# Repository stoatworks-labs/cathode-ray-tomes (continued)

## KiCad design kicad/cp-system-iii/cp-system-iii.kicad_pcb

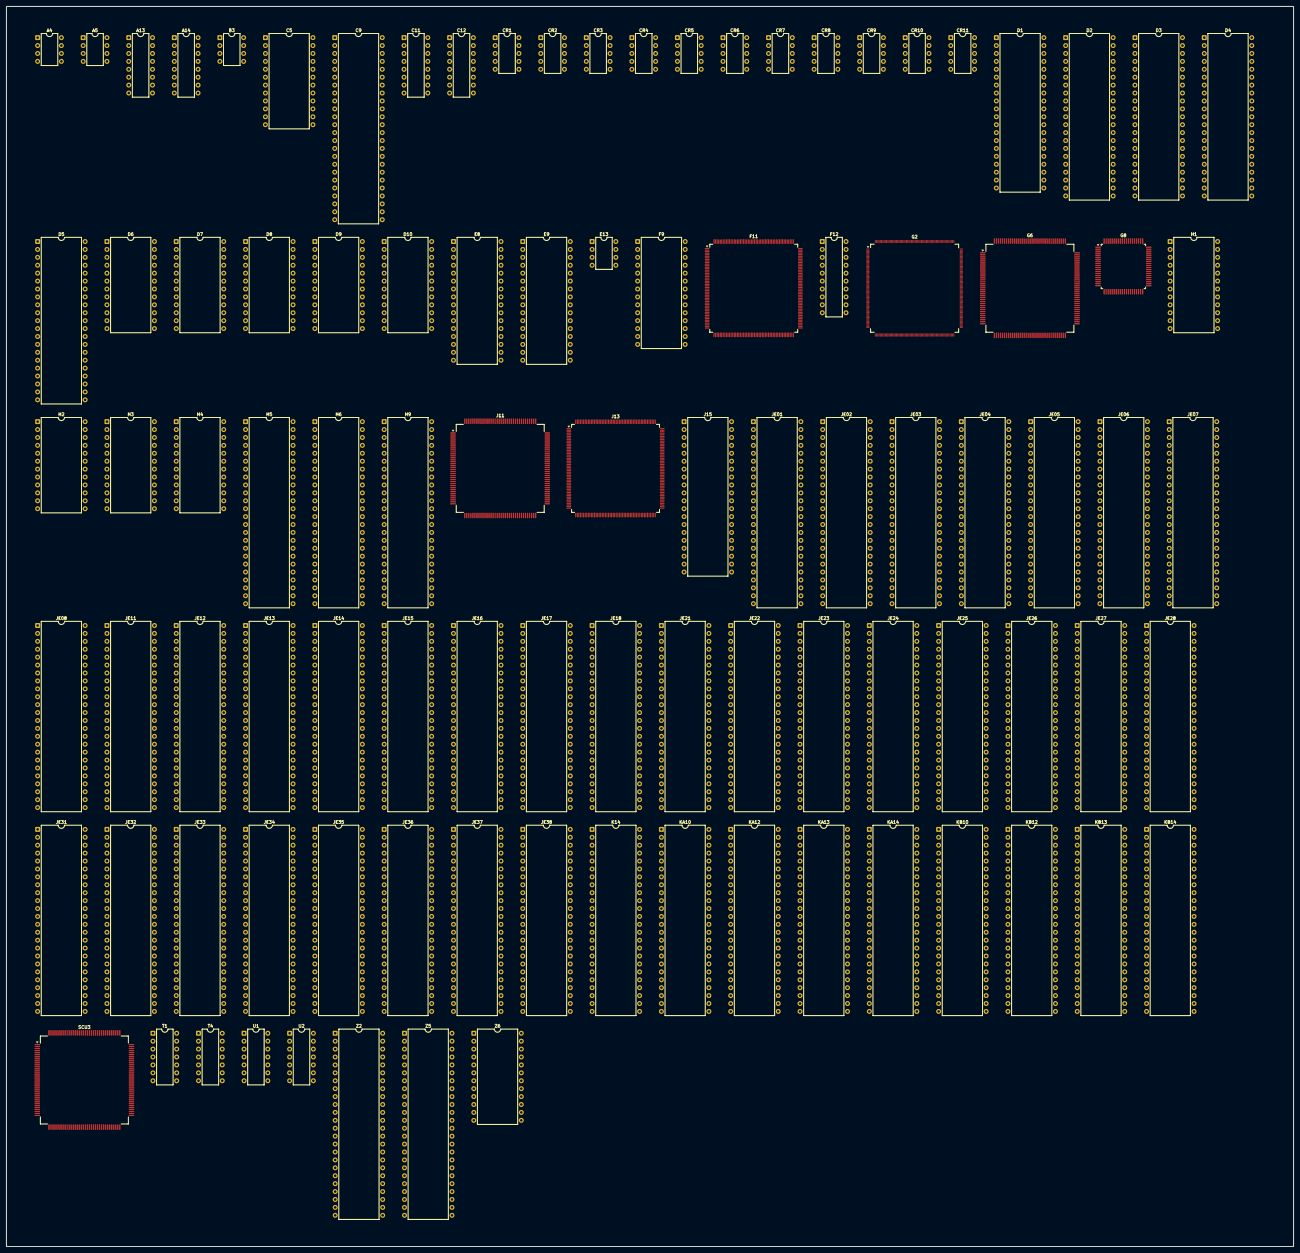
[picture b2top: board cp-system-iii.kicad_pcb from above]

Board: 2 copper layers, 413.0 x 397.9 mm, 98 parts (0 on the bottom side), 566 nets, no tracks yet.

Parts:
A4, A5: Opamp_Dual; DIP-8_W7.62mm
A13, A14: 2501; DIP-16_W7.62mm
B3: TA8201AK; DIP-8_W7.62mm
C5: TDA1306T; DIP-24_W15.24mm
C9: MC44200FT; DIP-48_W15.24mm
C11, C12: TD62064; DIP-16_W7.62mm
CR1, CR2, CR3, CR4, CR5, CR6, CR7, CR8, CR9, CR10, CR11: CRE438-60; DIP-10_W7.62mm
D1: MB814260-70PJ; DIP-40_W15.24mm
D2, D3, D4, D5: HM5118160AJ; DIP-42_W15.24mm
D6, D7, D8, D9, D10: CU383-69K; DIP-24_W15.24mm
E8, E9: HM628127HJP; DIP-32_W15.24mm
E13: AT93C46-10SC; DIP-8_W7.62mm
F9: N341256SJ_20; DIP-28_W15.24mm
F11: DL-2929-IOU; PQFP-208_28x28mm_P0.5mm
F12: 16103FPJ; DIP-20_W7.62mm
G2: DL-2729_PPU; PQFP-256_28x28mm_P0.4mm
G6: DL-3329-SSU; PQFP-144_28x28mm_P0.65mm
G8: DL-3529-GLL2; PQFP-80_14x14mm_P0.65mm
H1, H2, H3, H4: CU383-69K; DIP-24_W15.24mm
H5, H6, H9: 74FCT-16244ATPV; DIP-48_W15.24mm
J11: DL-3429-GLL1; PQFP-144_28x28mm_P0.65mm
J13: DL-2829-CCU; PQFP-208_28x28mm_P0.5mm
J15: MB814260-70PJ; DIP-40_W15.24mm
JE01, JE02, JE03, JE04, JE05, JE06, JE07, JE08, JE11, JE12, JE13, JE14, JE15, JE16, JE17, JE18, JE21, JE22, JE23, JE24, JE25, JE26, JE27, JE28, JE31, JE32, JE33, JE34, JE35, JE36, JE37, JE38: 29F016-90PFTN; DIP-48_W15.24mm
K14: Am33C93A; DIP-48_W15.24mm
KA10, KA12, KA13, KA14: 29F016-90PFTN; DIP-48_W15.24mm
KB10, KB12, KB13, KB14: 29F016-90PFTN; DIP-48_W15.24mm
SCU3: HD6417604F28_SH2; PQFP-144_28x28mm_P0.65mm
T1, T4: 7400; DIP-14_W7.62mm
U1, U2: 74LS08; DIP-14_W7.62mm
Z2: 29F400TA-90PF; DIP-48_W15.24mm
Z5: 28F400-200BX/BL; DIP-48_W15.24mm
Z6: FM1208S-250SC; DIP-24_W15.24mm

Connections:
+5V: SCU3.4, SCU3.12, SCU3.18, SCU3.24, SCU3.40, SCU3.48, SCU3.54, SCU3.60, SCU3.70, SCU3.71, SCU3.92, SCU3.112, SCU3.113, T4.4
/2GLL2CCU0: G8.74, J13.152
/2GLL2IOU0: F11.190, G8.75
/2GLL2PPU0: G2.13, G8.64
/2GLL2PPU1: G2.120, G8.66
/2GLL2PPU2: G2.119, G8.67
/2GLL2PPU3: G2.118, G8.68
/2GLL2PPU4: G2.117, G8.69
/2GLL2PPU5: G2.116, G8.70
/2GLL2PPU6: G2.121, G8.72
/2SPRITE_AB0: H9.3, JE31.30, JE32.30, JE33.30, JE34.30, JE35.30, JE36.30, JE37.30, JE38.30
/2SPRITE_AB1: H9.6, JE31.29, JE32.29, JE33.29, JE34.29, JE35.29, JE36.29, JE37.29, JE38.29
/2SPRITE_AB2: H9.9, JE31.28, JE32.28, JE33.28, JE34.28, JE35.28, JE36.28, JE37.28, JE38.28
/2SPRITE_AB3: H9.12, JE31.27, JE32.27, JE33.27, JE34.27, JE35.27, JE36.27, JE37.27, JE38.27
/2SPRITE_AB4: H9.14, JE31.22, JE32.22, JE33.22, JE34.22, JE35.22, JE36.22, JE37.22, JE38.22
/2SPRITE_AB5: H9.17, JE31.21, JE32.21, JE33.21, JE34.21, JE35.21, JE36.21, JE37.21, JE38.21
/2SPRITE_AB6: H9.20, JE31.20, JE32.20, JE33.20, JE34.20, JE35.20, JE36.20, JE37.20, JE38.20
/2SPRITE_AB7: H9.23, JE31.19, JE32.19, JE33.19, JE34.19, JE35.19, JE36.19, JE37.19, JE38.19
/2SPRITE_AB8: H6.3, JE31.18, JE32.18, JE33.18, JE34.18, JE35.18, JE36.18, JE37.18, JE38.18
/2SPRITE_AB9: H6.6, JE31.17, JE32.17, JE33.17, JE34.17, JE35.17, JE36.17, JE37.17, JE38.17
/2SPRITE_AB10: H6.9, JE31.16, JE32.16, JE33.16, JE34.16, JE35.16, JE36.16, JE37.16, JE38.16
/2SPRITE_AB11: H6.12, JE31.15, JE32.15, JE33.15, JE34.15, JE35.15, JE36.15, JE37.15, JE38.15
/2SPRITE_AB12: H6.14, JE31.10, JE32.10, JE33.10, JE34.10, JE35.10, JE36.10, JE37.10, JE38.10
/2SPRITE_AB13: H6.17, JE31.9, JE32.9, JE33.9, JE34.9, JE35.9, JE36.9, JE37.9, JE38.9
/2SPRITE_AB14: H6.20, JE31.8, JE32.8, JE33.8, JE34.8, JE35.8, JE36.8, JE37.8, JE38.8
/2SPRITE_AB15: H6.23, JE31.7, JE32.7, JE33.7, JE34.7, JE35.7, JE36.7, JE37.7, JE38.7
/2SPRITE_AB16: H5.3, JE31.6, JE32.6, JE33.6, JE34.6, JE35.6, JE36.6, JE37.6, JE38.6
/2SPRITE_AB17: H5.6, JE31.5, JE32.5, JE33.5, JE34.5, JE35.5, JE36.5, JE37.5, JE38.5
/2SPRITE_AB18: H5.9, JE31.4, JE32.4, JE33.4, JE34.4, JE35.4, JE36.4, JE37.4, JE38.4
/2SPRITE_AB19: H5.12, JE31.3, JE32.3, JE33.3, JE34.3, JE35.3, JE36.3, JE37.3, JE38.3
/2SPRITE_AB20: H5.14, JE31.46, JE32.46, JE33.46, JE34.46, JE35.46, JE36.46, JE37.46, JE38.46
/+12V: C11.1, C11.8, C12.1, C12.8
/APP0: D6.11, F11.99
/APP1: D6.14, F11.101
/APP2: D6.17, F11.100
/BCK: D6.3, G2.90
/BES_PPU2: D7.5, G2.14
/BIC_A0: G2.41, J13.56, K14.21
/BX_SPR: G8.57, H1.13, H2.13, H3.13, H4.13
/CPUC_A0: J13.6, SCU3.30, Z2.45
/CPUC_A1: J11.106, J13.7, SCU3.31, Z2.25, Z5.11, Z6.8
/CPUC_A2: J11.105, J13.8, SCU3.32, Z2.24, Z5.10, Z6.7
/CPUC_A3: J11.104, J13.9, SCU3.34, Z2.23, Z5.9, Z6.6
/CPUC_A4: J11.103, J13.11, SCU3.35, SCU3.36, Z2.21, Z2.22, Z5.7, Z5.8, Z6.4, Z6.5
/CPUC_A5: J11.102, J13.12
/CPUC_A6: J11.101, J13.13, SCU3.37, Z2.20, Z5.6, Z6.3
/CPUC_A7: J11.100, J13.14, SCU3.38, Z2.19, Z5.5, Z6.2
/CPUC_A8: J11.98, J13.16, SCU3.39, Z2.18, Z5.4, Z6.1
/CPUC_A9: J11.97, J13.17, SCU3.41, Z2.8, Z5.42, Z6.23
/CPUC_A10: J11.96, J13.18, SCU3.43, Z2.7, Z5.41
/CPUC_A11: J11.95, J13.19, SCU3.44, Z2.6, Z5.40
/CPUC_A12: J11.94, J13.20, SCU3.45, Z2.5, Z5.39
/CPUC_A13: J11.93, J13.21, SCU3.46, Z2.4, Z5.38
/CPUC_A14: J11.92, J13.22, SCU3.47, Z2.3, Z5.37
/CPUC_A15: J11.89, J13.23, SCU3.49, Z2.2, Z5.36
/CPUC_A16: J11.88, J13.24, SCU3.51, Z2.1, Z5.35
/CPUC_A17: J11.87, J13.25, SCU3.52, Z2.48, Z5.34
/CPUC_A18: J11.86, J13.27, SCU3.53, Z2.17, Z5.12
/CPUC_A19: J11.85, J13.28, SCU3.55
/CPUC_A20: J11.84, J13.29, SCU3.57
/CPUC_A21: J11.83, J13.30, SCU3.58
/CPUC_A22: J11.82, J13.31, SCU3.59
/CPUC_A23: J11.81, J13.32, SCU3.61
/CPUC_A24: J13.33, SCU3.63, T1.9
/CPUC_A25: J13.34, SCU3.64
/CPUC_A26: J13.35, SCU3.65
/CPUC_D0: J13.92, SCU3.130, Z2.29, Z6.9
/CPUC_D1: J13.91, SCU3.131, Z2.31, Z6.10
/CPUC_D2: J13.90, SCU3.133, Z2.33, Z6.11
/CPUC_D3: J13.89, SCU3.135, Z2.35, Z6.13
/CPUC_D4: J13.88, SCU3.136, Z2.38, Z6.14
/CPUC_D5: J13.87, SCU3.137, Z2.40, Z6.15
/CPUC_D6: J13.86, SCU3.138, Z2.42, Z6.16
/CPUC_D7: J13.85, SCU3.140, Z2.44, Z6.17
/CPUC_D8: J13.84, SCU3.142, Z2.30
/CPUC_D9: J13.83, SCU3.143, Z2.32
/CPUC_D10: J13.82, SCU3.144, Z2.34
/CPUC_D11: J13.81, SCU3.1, Z2.36
/CPUC_D12: J13.80, SCU3.2, Z2.39
/CPUC_D13: J13.79, SCU3.3, Z2.41
/CPUC_D14: J13.78, SCU3.5, Z2.43
/CPUC_D15: J13.77, SCU3.7
/CPUC_D16: J13.75, SCU3.8
/CPUC_D17: J13.74, SCU3.9
/CPUC_D18: J13.73, SCU3.10
/CPUC_D19: J13.72, SCU3.11
/CPUC_D20: J13.71, SCU3.13
/CPUC_D21: J13.70, SCU3.15
/CPUC_D22: J13.69, SCU3.16
/CPUC_D23: J13.68, SCU3.17
/CPUC_D24: J13.67, SCU3.19
/CPUC_D25: J13.66, SCU3.21
/CPUC_D26: J13.65, SCU3.22
/CPUC_D27: J13.64, SCU3.23
/CPUC_D28: J13.63, SCU3.25
/CPUC_D29: J13.62, SCU3.27
/CPUC_D30: J13.59, SCU3.28
/CPUC_D31: J13.58, SCU3.29
/CPUC_~CS0: J13.5, SCU3.72
/CPUC_~CS1: J13.4, SCU3.73, T1.13
/CPUC_~CS2: J13.3, SCU3.74
/CPUC_~CS3: J13.2, SCU3.75
/CPUC_~WE0: J13.41, SCU3.85, Z6.21
/CPUC_~WE1: J13.40, SCU3.83
/CPUC_~WE2: J13.39, SCU3.82
/CPUC_~WE3: J13.37, SCU3.81
/DRIVER_GLL0: G6.124, J11.138
/DRIVER_GLL1: F11.208, J11.123
/DRIVER_GLL2: G6.120, G8.61, J11.122
/DRIVER_GLL3: F11.48, J11.139
/DRIVER_GLL4: F11.3, J11.31
/GLL2CCU0: J11.79, J13.49
/GLL2CCU1: J11.56, J13.156
/GLL2CCU2: J11.108, J13.48
/GLL2CCU4: J11.129, J13.202
/GLL2CCU5: F11.111, J11.134
/MAIN_A0: F11.4, G2.23, G6.122, J11.133
/MAIN_A1: F11.5, G2.31, G6.123, J11.131
/MAIN_A2: F11.27, G2.32, G6.3, J11.132
/MAIN_A3: F11.26, G2.33, G6.2, J11.137
/MAIN_A4: F11.25, G2.34, G6.1, J11.57
/MAIN_A5: F11.24, G2.35, G6.144, J11.32, J13.155
/MAIN_A6: F11.23, G2.36, G6.143, J11.30
/MAIN_A7: F11.22, G2.37, G6.142, J11.29
/MAIN_A8: F11.21, G2.42, G6.141, J11.28
/MAIN_A9: F11.20, G2.43, G6.140, J11.27
/MAIN_A10: F11.19, G2.44, G6.139, J11.26
/MAIN_A11: F11.18, G2.45, G6.138, J11.24
/MAIN_A12: F11.17, G2.46, G6.137, J11.23
/MAIN_A13: F11.16, G2.47, G6.136, J11.22
/MAIN_A14: F11.14, G2.48, G6.135, J11.21
/MAIN_A15: F11.13, G2.49, G6.134, J11.20
/MAIN_A16: F11.12, G2.50, G6.133, J11.17
/MAIN_A17: F11.11, G2.51, G6.132, J11.16
/MAIN_A18: F11.9, G2.52, G6.131, J11.15
/MAIN_A19: F11.8, G2.53, J11.14
/MAIN_A20: F11.7, G2.54, J11.13
/MAIN_A21: G2.55, J11.12
/MAIN_A22: G2.56, J11.11
/MAIN_A23: G2.58, J11.10
/MAIN_A24: G2.59, J11.8
/MAIN_A25: G2.60, J11.7
/MAIN_A26: G2.61, J11.6
/MAIN_A27: G2.62, J11.5
/MAIN_A28: G2.63, J11.4
/MAIN_D0: F11.46, G2.64, G6.13, J11.53, K14.13
/MAIN_D1: F11.45, G2.65, G6.12, J11.52, K14.14
/MAIN_D2: F11.44, G2.66, G6.10, J11.51, K14.15
/MAIN_D3: F11.42, G2.67, G6.9, J11.50, K14.16
/MAIN_D4: F11.41, G2.69, G6.8, J11.49, K14.17
/MAIN_D5: F11.40, G2.70, G6.7, J11.48, K14.18
/MAIN_D6: F11.39, G2.72, G6.6, J11.46, K14.19
/MAIN_D7: F11.37, G2.73, G6.5, J11.45, K14.20
/MAIN_D8: F11.36, G2.75, J11.43
/MAIN_D9: F11.35, G2.78, J11.42
/MAIN_D10: F11.34, G2.80, J11.41
/MAIN_D11: F11.33, G2.81, J11.39
/MAIN_D12: F11.32, G2.83, J11.38
/MAIN_D13: F11.31, G2.84, J11.37
/MAIN_D14: F11.30, G2.86, J11.36
/MAIN_D15: F11.29, G2.87, J11.35
/PAL0: D10.21, E9.6, G2.192
/PAL1: D10.17, E9.7, G2.189
/PAL2: D10.11, E9.10, G2.188
/PAL3: D10.7, E9.11, G2.187
/PAL4: D10.3, E9.22, G2.186
/PAL5: D9.21, E9.23, G2.185
/PAL6: D9.17, E9.26, G2.184
/PAL8: D9.11, E8.6, G2.183
/PAL9: D9.7, E8.7, G2.182
/PAL10: D9.3, E8.10, G2.180
/PAL11: D8.21, E8.11, G2.179
/PAL12: D8.17, E8.22, G2.178
/PAL13: D8.11, E8.23, G2.177
/PAL14: D8.7, E8.26, G2.176
/PAL15: D8.3, E8.27, G2.175
/PPU2CCU0: G2.40, J13.57
/PPU2SSU0: G2.27, G6.17
/RD/~WR_CPUC: J11.80, J13.46, SCU3.77
/SCR_A0: G2.128, H1.3
/SCR_A1: G2.129, H1.7
/SCR_A2: G2.130, H1.11
/SCR_A3: G2.131, H1.17
/SCR_A4: G2.124, H2.3
/SCR_A5: G2.125, H2.7
/SCR_A6: G2.126, H2.11
/SCR_A7: G2.127, H2.17
/SCR_A8: G2.132, H4.3
/SCR_A9: G2.134, H4.7
/SCR_A10: G2.135, H4.11
/SCR_A11: G2.136, H4.17
/SCR_A12: G2.137, H3.3
/SCR_A13: G2.138, H3.7
/SCR_A14: G2.139, H3.11
/SCR_A15: G2.140, H3.17
/SHD0: J11.75, J13.113, J15.2, KA14.31, KB14.31
/SHD1: J11.74, J15.3, KA14.32, KB14.32
/SHD2: J11.73, J15.4, KA14.33, KB14.33
/SHD3: J11.72, J13.117, J15.5, KA14.34, KB14.34
/SHD4: J11.71, J13.118, J15.7, KA14.38, KB14.38
/SHD5: J11.70, J13.120, J15.8, KA14.39, KB14.39
/SHD6: J11.69, J13.121, J15.9, KA14.40, KB14.40
/SHD7: J11.68, J13.122, J15.10, KA14.41, KB14.41
/SHD8: J11.66, J13.123, J15.31, KA13.31, KB13.31
/SHD9: J11.65, J13.124, J15.32, KA13.32, KB13.32
/SHD10: J11.64, J13.125, J15.33, KA13.33, KB13.33
/SHD11: J11.63, J13.126, J15.34, KA13.34, KB13.34
/SHD12: J11.62, J13.127, J15.36, KA13.38, KB13.38
/SHD13: J11.61, J13.128, J15.37, KA13.39, KB13.39
/SHD14: J11.60, J13.130, J15.38, KA13.40, KB13.40
/SHD15: J11.59, J13.131, J15.39, KA13.41, KB13.41
/SNDD: D6.7, G2.88
/SND_A0: J13.180, KA10.30, KA12.30, KA13.30, KA14.30, KB10.30, KB12.30, KB13.30, KB14.30
/SND_A1: J13.179, KA10.29, KA12.29, KA13.29, KA14.29, KB10.29, KB12.29, KB13.29, KB14.29
/SND_A2: J13.178, KA10.28, KA12.28, KA13.28, KA14.28, KB10.28, KB12.28, KB13.28, KB14.28
/SND_A3: J13.177, KA10.27, KA12.27, KA13.27, KA14.27, KB10.27, KB12.27, KB13.27, KB14.27
/SND_A4: J13.176, KA10.22, KA12.22, KA13.22, KA14.22, KB10.22, KB12.22, KB13.22, KB14.22
/SND_A5: J13.175, KA10.21, KA12.21, KA13.21, KA14.21, KB10.21, KB12.21, KB13.21, KB14.21
/SND_A6: J13.173, KA10.20, KA12.20, KA13.20, KA14.20, KB10.20, KB12.20, KB13.20, KB14.20
/SND_A7: J13.172, KA10.19, KA12.19, KA13.19, KA14.19, KB10.19, KB12.19, KB13.19, KB14.19
/SND_A8: J13.171, KA10.18, KA12.18, KA13.18, KA14.18, KB10.18, KB12.18, KB13.18, KB14.18
/SND_A9: J13.170, KA10.17, KA12.17, KA13.17, KA14.17, KB10.17, KB12.17, KB13.17, KB14.17
/SND_A10: J13.169, KA10.16, KA12.16, KA13.16, KA14.16, KB10.16, KB12.16, KB13.16, KB14.16
/SND_A11: J13.168, KA10.15, KA12.15, KA13.15, KA14.15, KB10.15, KB12.15, KB13.15, KB14.15
/SND_A12: J13.167, KA10.10, KA12.10, KA13.10, KA14.10, KB10.10, KB12.10, KB13.10, KB14.10
/SND_A13: J13.166, KA10.9, KA12.9, KA13.9, KA14.9, KB10.9, KB12.9, KB13.9, KB14.9
/SND_A14: J13.163, KA10.8, KA12.8, KA13.8, KA14.8, KB10.8, KB12.8, KB13.8, KB14.8
/SND_A15: J13.162, KA10.7, KA12.7, KA13.7, KA14.7, KB10.7, KB12.7, KB13.7, KB14.7
/SND_A16: J13.161, KA10.6, KA12.6, KA13.6, KA14.6, KB10.6, KB12.6, KB13.6, KB14.6
/SND_A17: J13.160, KA10.5, KA12.5, KA13.5, KA14.5, KB10.5, KB12.5, KB13.5, KB14.5
/SND_A18: J13.159, KA10.4, KA12.4, KA13.4, KA14.4, KB10.4, KB12.4, KB13.4, KB14.4
/SND_A19: J13.158, KA10.3, KA12.3, KA13.3, KA14.3, KB10.3, KB12.3, KB13.3, KB14.3
/SND_A20: J13.157, KA10.46, KA12.46, KA13.46, KA14.46, KB10.46, KB12.46, KB13.46, KB14.46
/SND_AD0: J13.140, KA10.31, KB10.31
/SND_AD1: J13.141, KA10.32, KB10.32
/SND_AD2: J13.143, KA10.33, KB10.33
/SND_AD3: J13.144, KA10.34, KB10.34
/SND_AD4: J13.145, KA10.38, KB10.38
/SND_AD5: J13.146, KA10.39, KB10.39
/SND_AD6: J13.148, KA10.40, KB10.40
/SND_AD7: J13.149, KA10.41, KB10.41
/SND_AD8: J13.132, KA12.31, KB12.31
/SND_AD9: J13.133, KA12.32, KB12.32
/SND_AD10: J13.134, KA12.33, KB12.33
/SND_AD11: J13.135, KA12.34, KB12.34
/SND_AD12: J13.136, KA12.38, KB12.38
/SND_AD13: J13.137, KA12.39, KB12.39
/SND_AD14: J13.138, KA12.40, KB12.40
/SND_AD15: J13.139, KA12.41, KB12.41
/SPRITE_AB0: H9.2, JE01.30, JE02.30, JE03.30, JE04.30, JE05.30, JE06.30, JE07.30, JE08.30, JE11.30, JE12.30, JE13.30, JE14.30, JE15.30, JE16.30, JE17.30, JE18.30, JE21.30, JE22.30, JE23.30, JE24.30, JE25.30, JE26.30, JE27.30, JE28.30
/SPRITE_AB1: H9.5, JE01.29, JE02.29, JE03.29, JE04.29, JE05.29, JE06.29, JE07.29, JE08.29, JE11.29, JE12.29, JE13.29, JE14.29, JE15.29, JE16.29, JE17.29, JE18.29, JE21.29, JE22.29, JE23.29, JE24.29, JE25.29, JE26.29, JE27.29, JE28.29
/SPRITE_AB2: H9.8, JE01.28, JE02.28, JE03.28, JE04.28, JE05.28, JE06.28, JE07.28, JE08.28, JE11.28, JE12.28, JE13.28, JE14.28, JE15.28, JE16.28, JE17.28, JE18.28, JE21.28, JE22.28, JE23.28, JE24.28, JE25.28, JE26.28, JE27.28, JE28.28
/SPRITE_AB3: H9.11, JE01.27, JE02.27, JE03.27, JE04.27, JE05.27, JE06.27, JE07.27, JE08.27, JE11.27, JE12.27, JE13.27, JE14.27, JE15.27, JE16.27, JE17.27, JE18.27, JE21.27, JE22.27, JE23.27, JE24.27, JE25.27, JE26.27, JE27.27, JE28.27
/SPRITE_AB4: H9.13, JE01.22, JE02.22, JE03.22, JE04.22, JE05.22, JE06.22, JE07.22, JE08.22, JE11.22, JE12.22, JE13.22, JE14.22, JE15.22, JE16.22, JE17.22, JE18.22, JE21.22, JE22.22, JE23.22, JE24.22, JE25.22, JE26.22, JE27.22, JE28.22
/SPRITE_AB5: H9.16, JE01.21, JE02.21, JE03.21, JE04.21, JE05.21, JE06.21, JE07.21, JE08.21, JE11.21, JE12.21, JE13.21, JE14.21, JE15.21, JE16.21, JE17.21, JE18.21, JE21.21, JE22.21, JE23.21, JE24.21, JE25.21, JE26.21, JE27.21, JE28.21
/SPRITE_AB6: H9.19, JE01.20, JE02.20, JE03.20, JE04.20, JE05.20, JE06.20, JE07.20, JE08.20, JE11.20, JE12.20, JE13.20, JE14.20, JE15.20, JE16.20, JE17.20, JE18.20, JE21.20, JE22.20, JE23.20, JE24.20, JE25.20, JE26.20, JE27.20, JE28.20
/SPRITE_AB7: H9.22, JE01.19, JE02.19, JE03.19, JE04.19, JE05.19, JE06.19, JE07.19, JE08.19, JE11.19, JE12.19, JE13.19, JE14.19, JE15.19, JE16.19, JE17.19, JE18.19, JE21.19, JE22.19, JE23.19, JE24.19, JE25.19, JE26.19, JE27.19, JE28.19
/SPRITE_AB8: H6.2, JE01.18, JE02.18, JE03.18, JE04.18, JE05.18, JE06.18, JE07.18, JE08.18, JE11.18, JE12.18, JE13.18, JE14.18, JE15.18, JE16.18, JE17.18, JE18.18, JE21.18, JE22.18, JE23.18, JE24.18, JE25.18, JE26.18, JE27.18, JE28.18
/SPRITE_AB9: H6.5, JE01.17, JE02.17, JE03.17, JE04.17, JE05.17, JE06.17, JE07.17, JE08.17, JE11.17, JE12.17, JE13.17, JE14.17, JE15.17, JE16.17, JE17.17, JE18.17, JE21.17, JE22.17, JE23.17, JE24.17, JE25.17, JE26.17, JE27.17, JE28.17
/SPRITE_AB10: H6.8, JE01.16, JE02.16, JE03.16, JE04.16, JE05.16, JE06.16, JE07.16, JE08.16, JE11.16, JE12.16, JE13.16, JE14.16, JE15.16, JE16.16, JE17.16, JE18.16, JE21.16, JE22.16, JE23.16, JE24.16, JE25.16, JE26.16, JE27.16, JE28.16
/SPRITE_AB11: H6.11, JE01.15, JE02.15, JE03.15, JE04.15, JE05.15, JE06.15, JE07.15, JE08.15, JE11.15, JE12.15, JE13.15, JE14.15, JE15.15, JE16.15, JE17.15, JE18.15, JE21.15, JE22.15, JE23.15, JE24.15, JE25.15, JE26.15, JE27.15, JE28.15
/SPRITE_AB12: H6.13, JE01.10, JE02.10, JE03.10, JE04.10, JE05.10, JE06.10, JE07.10, JE08.10, JE11.10, JE12.10, JE13.10, JE14.10, JE15.10, JE16.10, JE17.10, JE18.10, JE21.10, JE22.10, JE23.10, JE24.10, JE25.10, JE26.10, JE27.10, JE28.10
/SPRITE_AB13: H6.16, JE01.9, JE02.9, JE03.9, JE04.9, JE05.9, JE06.9, JE07.9, JE08.9, JE11.9, JE12.9, JE13.9, JE14.9, JE15.9, JE16.9, JE17.9, JE18.9, JE21.9, JE22.9, JE23.9, JE24.9, JE25.9, JE26.9, JE27.9, JE28.9
/SPRITE_AB14: H6.19, JE01.8, JE02.8, JE03.8, JE04.8, JE05.8, JE06.8, JE07.8, JE08.8, JE11.8, JE12.8, JE13.8, JE14.8, JE15.8, JE16.8, JE17.8, JE18.8, JE21.8, JE22.8, JE23.8, JE24.8, JE25.8, JE26.8, JE27.8, JE28.8
/SPRITE_AB15: H6.22, JE01.7, JE02.7, JE03.7, JE04.7, JE05.7, JE06.7, JE07.7, JE08.7, JE11.7, JE12.7, JE13.7, JE14.7, JE15.7, JE16.7, JE17.7, JE18.7, JE21.7, JE22.7, JE23.7, JE24.7, JE25.7, JE26.7, JE27.7, JE28.7
/SPRITE_AB16: H5.2, JE01.6, JE02.6, JE03.6, JE04.6, JE05.6, JE06.6, JE07.6, JE08.6, JE11.6, JE12.6, JE13.6, JE14.6, JE15.6, JE16.6, JE17.6, JE18.6, JE21.6, JE22.6, JE23.6, JE24.6, JE25.6, JE26.6, JE27.6, JE28.6
/SPRITE_AB17: H5.5, JE01.5, JE02.5, JE03.5, JE04.5, JE05.5, JE06.5, JE07.5, JE08.5, JE11.5, JE12.5, JE13.5, JE14.5, JE15.5, JE16.5, JE17.5, JE18.5, JE21.5, JE22.5, JE23.5, JE24.5, JE25.5, JE26.5, JE27.5, JE28.5
/SPRITE_AB18: H5.8, JE01.4, JE02.4, JE03.4, JE04.4, JE05.4, JE06.4, JE07.4, JE08.4, JE11.4, JE12.4, JE13.4, JE14.4, JE15.4, JE16.4, JE17.4, JE18.4, JE21.4, JE22.4, JE23.4, JE24.4, JE25.4, JE26.4, JE27.4, JE28.4
/SPRITE_AB19: H5.11, JE01.3, JE02.3, JE03.3, JE04.3, JE05.3, JE06.3, JE07.3, JE08.3, JE11.3, JE12.3, JE13.3, JE14.3, JE15.3, JE16.3, JE17.3, JE18.3, JE21.3, JE22.3, JE23.3, JE24.3, JE25.3, JE26.3, JE27.3, JE28.3
/SPRITE_AB20: H5.13, JE01.46, JE02.46, JE03.46, JE04.46, JE05.46, JE06.46, JE07.46, JE08.46, JE11.46, JE12.46, JE13.46, JE14.46, JE15.46, JE16.46, JE17.46, JE18.46, JE21.46, JE22.46, JE23.46, JE24.46, JE25.46, JE26.46, JE27.46, JE28.46
/SSU_A0: G2.148, G6.36
/SSU_A1: G2.149, G6.35
/SSU_A2: G2.151, G6.34
/SSU_A3: G2.154, G6.33
/SSU_A4: G2.156, G6.32
/SSU_A5: G2.157, G6.31
/SSU_A6: G2.159, G6.30
/SSU_A7: G2.160, G6.29
/SSU_A8: G2.162, G6.28
/SSU_A9: G2.163, G6.27
/SSU_A10: G2.164, G6.26
/SSU_A11: G2.165, G6.25
/SSU_A12: G2.166, G6.24
/SSU_A13: G2.167, G6.23
/SSU_A14: G2.168, G6.22
/SSU_A15: G2.169, G6.21
/SSU_A16: G2.170, G6.20
/SU2IO0: F11.49, G6.121
/SYNCA: G2.28, G6.16, U1.2
/SYNCB: G2.29, G6.15, U1.1
/SYSCLK: D6.8, G2.91
/WAIT_CPUC: J13.52, T1.2
/WS: D6.4, G2.89
/cassette/MD: SCU3.117, SCU3.119, T4.6
/cassette/~BYTE: Z2.47, Z5.33
/cassette/~CE_FRAM: T1.5, T1.8, Z6.18
/cassette/~OE_CMOS: Z2.28, Z5.14
/cassette/~RST_CMOS: Z2.12, Z5.44
/cassette/~WAIT_CPUC: T1.3, T1.4
/cassette/~WAIT: SCU3.89, T1.6
/iou/1DSD_I1: C12.3, F11.203
/iou/1DSD_I2: C12.6, F11.204
/iou/1DSD_I3: C12.11, F11.205
/iou/1DSD_I4: C12.14, F11.206
/iou/2DSD_I3: C11.11, F11.199
/iou/2DSD_I4: C11.14, F11.202
/iou/CLL2_0: A13.2, A14.16
/iou/CLL2_1: A13.4, A14.14
/iou/CLL2_2: A13.6, A14.12
/iou/CLL2_3: A13.8, A14.10
/iou/P_C0: A13.16, F11.116
/iou/P_C1: A13.12, F11.117
/iou/P_C2: A13.14, F11.125
/iou/P_C3: A13.10, F11.126
/ppu/FB_A0: D2.17, D3.17, D4.17, D5.17
/ppu/FB_A1: D2.18, D3.18, D4.18, D5.18
/ppu/FB_A2: D2.19, D3.19, D4.19, D5.19
/ppu/FB_A3: D2.20, D3.20, D4.20, D5.20
/ppu/FB_A4: D2.23, D3.23, D4.23, D5.23
/ppu/FB_A5: D2.24, D3.24, D4.24, D5.24
/ppu/FB_A6: D2.25, D3.25, D4.25, D5.25
/ppu/FB_A7: D2.26, D3.26, D4.26, D5.26
/ppu/FB_A8: D3.27, D4.27, D5.27
/ppu/FB_A9: D3.28, D4.28, D5.28
/ppu/FB_D0: D2.2, D3.2
/ppu/FB_D1: D2.3, D3.3
/ppu/FB_D2: D2.4, D3.4
/ppu/FB_D3: D2.5, D3.5
/ppu/FB_D4: D2.7, D3.7
/ppu/FB_D5: D2.8, D3.8
/ppu/FB_D6: D2.9, D3.9
/ppu/FB_D7: D2.10, D3.10
/ppu/FB_D8: D2.33, D3.33
/ppu/FB_D9: D2.34, D3.34
/ppu/FB_D10: D2.35, D3.35
/ppu/FB_D11: D2.36, D3.36
/ppu/FB_D12: D2.38, D3.38
/ppu/FB_D13: D2.39, D3.39
/ppu/FB_D14: D2.40, D3.40
/ppu/FB_D15: D2.41, D3.41
/ppu/FB_D16: D4.2, D5.2
/ppu/FB_D17: D4.3, D5.3
/ppu/FB_D18: D4.4, D5.4
/ppu/FB_D19: D4.5, D5.5
/ppu/FB_D20: D4.7, D5.7
/ppu/FB_D21: D4.8, D5.8
/ppu/FB_D22: D4.9, D5.9
/ppu/FB_D23: D4.10, D5.10
/ppu/FB_D24: D4.33, D5.33
/ppu/FB_D25: D4.34, D5.34, G2.2
/ppu/FB_D26: D4.35, D5.35, G2.4
/ppu/FB_D27: D4.36, D5.36, G2.5
/ppu/FB_D28: D4.38, D5.38, G2.7
/ppu/FB_D29: D4.39, D5.39, G2.8
/ppu/FB_D30: D4.40, D5.40, G2.10
/ppu/FB_D31: D4.41, D5.41, G2.11
/ppu/OE_A: D2.29, D4.29
/ppu/OE_B: D3.29, D5.29
/ppu/RAMD0: D1.2, G2.207
/ppu/RAMD1: D1.3, G2.208
/ppu/RAMD2: D1.4, G2.211
/ppu/RAMD3: D1.5, G2.212
/ppu/RAMD4: D1.7, G2.213
/ppu/RAMD5: D1.8, G2.214
/ppu/RAMD6: D1.9, G2.215
/ppu/RAMD7: D1.10, G2.216
/ppu/RAMD8: D1.31, G2.217
/ppu/RAMD9: D1.32, G2.218
/ppu/RAMD10: D1.33, G2.219
/ppu/RAMD11: D1.34, G2.222
/ppu/RAMD12: D1.36, G2.223
/ppu/RAMD13: D1.37, G2.224
/ppu/RAMD14: D1.38, G2.225
/ppu/RAMD15: D1.39, G2.227
/ppu/SPRITE_A0: G2.92, H9.46, H9.47
/ppu/SPRITE_A1: G2.93, H9.43, H9.44
/ppu/SPRITE_A2: G2.94, H9.40, H9.41
/ppu/SPRITE_A3: G2.95, H9.37, H9.38
/ppu/SPRITE_A4: G2.97, H9.35, H9.36
/ppu/SPRITE_A5: G2.98, H9.32, H9.33
/ppu/SPRITE_A6: G2.99, H9.29, H9.30
/ppu/SPRITE_A7: G2.100, H9.26, H9.27
/ppu/SPRITE_A8: G2.101, H6.46, H6.47
/ppu/SPRITE_A9: G2.102, H6.43, H6.44
/ppu/SPRITE_A10: G2.103, H6.40, H6.41
/ppu/SPRITE_A11: G2.104, H6.37, H6.38
/ppu/SPRITE_A12: G2.105, H6.35, H6.36
/ppu/SPRITE_A13: G2.106, H6.32, H6.33
/ppu/SPRITE_A14: G2.107, H6.29, H6.30
/ppu/SPRITE_A15: G2.108, H6.26, H6.27
/ppu/SPRITE_A16: G2.109, H5.46, H5.47
/ppu/SPRITE_A17: G2.110, H5.43, H5.44
/ppu/SPRITE_A18: G2.111, H5.40, H5.41
/ppu/SPRITE_A19: G2.112, H5.37, H5.38
/ppu/SPRITE_A20: G2.113, H5.35, H5.36
/ppu/~RAS_MAIN: D3.14, D4.14, D5.14, G2.230
/ppu/~WE_PPU_A: D2.13, D4.13
/ppu/~WE_PPU_B: D3.13, D5.13
/simms_flash/2SPR2SCR_D0: H1.5, JE31.31, JE32.31, JE33.31, JE34.31, JE35.31, JE36.31, JE37.31, JE38.31
/simms_flash/2SPR2SCR_D1: H1.9, JE31.32, JE32.32, JE33.32, JE34.32, JE35.32, JE36.32, JE37.32, JE38.32
/simms_flash/2SPR2SCR_D2: H1.15, JE31.33, JE32.33, JE33.33, JE34.33, JE35.33, JE36.33, JE37.33, JE38.33
/simms_flash/2SPR2SCR_D3: H1.19, JE31.34, JE32.34, JE33.34, JE34.34, JE35.34, JE36.34, JE37.34, JE38.34
/simms_flash/2SPR2SCR_D4: H2.5, JE31.38, JE32.38, JE33.38, JE34.38, JE35.38, JE36.38, JE37.38, JE38.38
/simms_flash/2SPR2SCR_D5: H2.9, JE31.39, JE32.39, JE33.39, JE34.39, JE35.39, JE36.39, JE37.39, JE38.39
/simms_flash/2SPR2SCR_D6: H2.15, JE31.40, JE32.40, JE33.40, JE34.40, JE35.40, JE36.40, JE37.40, JE38.40
/simms_flash/2SPR2SCR_D7: H2.19, JE31.41, JE32.41, JE33.41, JE34.41, JE35.41, JE36.41, JE37.41, JE38.41
/simms_flash/SPR2SCR_D0: H1.2, JE01.31, JE02.31, JE03.31, JE04.31, JE05.31, JE06.31, JE07.31, JE08.31, JE11.31, JE12.31, JE13.31, JE14.31, JE15.31, JE16.31, JE17.31, JE18.31, JE21.31, JE22.31, JE23.31, JE24.31, JE25.31, JE26.31, JE27.31, JE28.31
/simms_flash/SPR2SCR_D1: H1.6, JE01.32, JE02.32, JE03.32, JE04.32, JE05.32, JE06.32, JE07.32, JE08.32, JE11.32, JE12.32, JE13.32, JE14.32, JE15.32, JE16.32, JE17.32, JE18.32, JE21.32, JE22.32, JE23.32, JE24.32, JE25.32, JE26.32, JE27.32, JE28.32
/simms_flash/SPR2SCR_D2: H1.10, JE01.33, JE02.33, JE03.33, JE04.33, JE05.33, JE06.33, JE07.33, JE08.33, JE11.33, JE12.33, JE13.33, JE14.33, JE15.33, JE16.33, JE17.33, JE18.33, JE21.33, JE22.33, JE23.33, JE24.33, JE25.33, JE26.33, JE27.33, JE28.33
/simms_flash/SPR2SCR_D3: H1.16, JE01.34, JE02.34, JE03.34, JE04.34, JE05.34, JE06.34, JE07.34, JE08.34, JE11.34, JE12.34, JE13.34, JE14.34, JE15.34, JE16.34, JE17.34, JE18.34, JE21.34, JE22.34, JE23.34, JE24.34, JE25.34, JE26.34, JE27.34, JE28.34
/simms_flash/SPR2SCR_D4: H2.2, JE01.38, JE02.38, JE03.38, JE04.38, JE05.38, JE06.38, JE07.38, JE08.38, JE11.38, JE12.38, JE13.38, JE14.38, JE15.38, JE16.38, JE17.38, JE18.38, JE21.38, JE22.38, JE23.38, JE24.38, JE25.38, JE26.38, JE27.38, JE28.38
/simms_flash/SPR2SCR_D5: H2.6, JE01.39, JE02.39, JE03.39, JE04.39, JE05.39, JE06.39, JE07.39, JE08.39, JE11.39, JE12.39, JE13.39, JE14.39, JE15.39, JE16.39, JE17.39, JE18.39, JE21.39, JE22.39, JE23.39, JE24.39, JE25.39, JE26.39, JE27.39, JE28.39
/simms_flash/SPR2SCR_D6: H2.10, JE01.40, JE02.40, JE03.40, JE04.40, JE05.40, JE06.40, JE07.40, JE08.40, JE11.40, JE12.40, JE13.40, JE14.40, JE15.40, JE16.40, JE17.40, JE18.40, JE21.40, JE22.40, JE23.40, JE24.40, JE25.40, JE26.40, JE27.40, JE28.40
/simms_flash/SPR2SCR_D7: H2.16, JE01.41, JE02.41, JE03.41, JE04.41, JE05.41, JE06.41, JE07.41, JE08.41, JE11.41, JE12.41, JE13.41, JE14.41, JE15.41, JE16.41, JE17.41, JE18.41, JE21.41, JE22.41, JE23.41, JE24.41, JE25.41, JE26.41, JE27.41, JE28.41
/ssu/A0: F9.10, G6.108
/ssu/A1: F9.9, G6.107
/ssu/A2: F9.8, G6.105
/ssu/A3: F9.7, G6.104
/ssu/A4: F9.6, G6.103
/ssu/A5: F9.5, G6.102
/ssu/A6: F9.4, G6.99
/ssu/A7: F9.3, G6.98
/ssu/A8: F9.25, G6.97
/ssu/A9: F9.24, G6.96
/ssu/A10: F9.21, G6.94
/ssu/A11: F9.23, G6.93
/ssu/A12: F9.2, G6.92
/ssu/A13: F9.26, G6.89
/ssu/A14: F9.1, G6.88
/ssu/D0: F9.11, G6.119
/ssu/D1: F9.12, G6.118
/ssu/D2: F9.13, G6.117
/ssu/D3: F9.15, G6.116
/ssu/D4: F9.16, G6.114
/ssu/D5: F9.17, G6.115
/ssu/D6: F9.18, G6.111
/ssu/D7: F9.19, G6.110
/ssu/~WE_SSU: F9.27, G6.109
/video_dac/A0: E8.4, E9.4
/video_dac/A1: E8.3, E9.3
/video_dac/A2: E8.2, E9.2
/video_dac/A3: E8.1, E9.1
/video_dac/A4: E8.32, E9.32
/video_dac/A5: E8.31, E9.31
/video_dac/A6: E8.30, E9.30
/video_dac/A7: E8.29, E9.29
/video_dac/A8: E8.21, E9.21
/video_dac/A9: E8.20, E9.20
/video_dac/A10: E8.19, E9.19
/video_dac/A11: E8.18, E9.18
/video_dac/A12: E8.17, E9.17
/video_dac/A13: E8.16, E9.16
/video_dac/A14: E8.15, E9.15
/video_dac/A15: E8.14, E9.14
/video_dac/A16: E8.13, E9.13
/video_dac/~WE_VD: E8.12, E9.12
/~BE: D7.1, D8.1, D9.1, D10.1
/~BLK: D8.13, D9.13, D10.13, G2.21
/~BS_CPUC: J13.42, SCU3.76
/~CEA: G8.48, JE31.11, JE34.11
/~CEB: G8.47, JE32.11, JE33.11
/~CEC: G8.45, JE35.11, JE38.11
/~CED: G8.44, JE36.11, JE37.11
/~CEE: G8.43, JE21.11, JE24.11
/~CEF: G8.42, JE22.11, JE23.11
/~CEG: G8.40, JE25.11, JE28.11
/~CEH: G8.39, JE26.11, JE27.11
/~CEI: G8.38, JE11.11, JE14.11
/~CEJ: G8.37, JE12.11, JE13.11
/~CEK: G8.35, JE15.11, JE18.11
/~CEL: G8.34, JE16.11, JE17.11
/~CEM: G8.32, JE01.11, JE04.11
/~CEN: G8.31, JE02.11, JE03.11
/~CEO: G8.30, JE05.11, JE08.11
/~CEP: G8.29, JE06.11, JE07.11
/~CE_S1: J13.195, KB10.11, KB12.11, KB13.11, KB14.11
/~CE_S2: J13.194, KA10.11, KA12.11, KA13.11, KA14.11
/~CER_CST: J13.154, T1.12, Z2.26
/~CS_GLL1: J11.116, K14.24
/~IRL0_CPUC: J11.114, SCU3.129
/~IRL1_CPUC: J11.113, SCU3.128
/~IRL2_CPUC: J11.112, SCU3.127
/~IRL3_CPUC: J11.111, SCU3.126
/~MR_GLL1: J11.121, K14.40
/~OEB: G8.17, JE31.43, JE32.43, JE33.43, JE34.43, JE35.43, JE36.43, JE37.43, JE38.43
/~OEC: G8.15, JE21.43, JE22.43, JE23.43, JE24.43, JE25.43, JE26.43, JE27.43, JE28.43
/~OED: G8.11, JE11.43, JE12.43, JE13.43, JE14.43, JE15.43, JE16.43, JE17.43, JE18.43
/~OEE: G8.9, JE01.43, JE02.43, JE03.43, JE04.43, JE05.43, JE06.43, JE07.43, JE08.43
/~OE_CCU: J13.196, KA10.43, KA12.43, KA13.43, KA14.43, KB10.43, KB12.43, KB13.43, KB14.43
/~RD_CPUC: J13.1, SCU3.87
/~RESET0: G8.78, JE01.14, JE02.14, JE03.14, JE04.14, JE05.14, JE06.14, JE07.14, JE08.14
/~RESET1: G8.79, JE11.14, JE12.14, JE13.14, JE14.14, JE15.14, JE16.14, JE17.14, JE18.14
/~RESET2: G8.80, JE21.14, JE22.14, JE23.14, JE24.14, JE25.14, JE26.14, JE27.14, JE28.14
/~RESET3: G8.2, JE31.14, JE32.14, JE33.14, JE34.14, JE35.14, JE36.14, JE37.14, JE38.14
/~RESET5: F11.189, KA10.14, KA12.14, KA13.14, KA14.14, KB10.14, KB12.14, KB13.14, KB14.14
/~RE_GLL1: J11.118, K14.26
/~RST_WD: J11.78, T4.12
/~STBY_WD: F12.19, T4.5
/~WEB: G8.19, JE31.44, JE32.44, JE33.44, JE34.44, JE35.44, JE36.44, JE37.44, JE38.44
/~WEC: G8.16, JE21.44, JE22.44, JE23.44, JE24.44, JE25.44, JE26.44, JE27.44, JE28.44
/~WED: G8.14, JE11.44, JE12.44, JE13.44, JE14.44, JE15.44, JE16.44, JE17.44, JE18.44
/~WEE: G8.10, JE01.44, JE02.44, JE03.44, JE04.44, JE05.44, JE06.44, JE07.44, JE08.44
/~WE_CCU: J13.192, KA10.44, KA12.44, KA13.44, KA14.44, KB10.44, KB12.44, KB13.44, KB14.44
/~WE_CMOS: Z2.11, Z5.43
/~WE_GLL1: J11.117, K14.25
unnamed: A4.3, A4.5
unnamed: A4.6, A4.7
unnamed: A5.3, A5.5
unnamed: A5.6, A5.7
unnamed: C5.1, C5.8, C5.10, C5.24
unnamed: C9.28, C9.29, C9.30
unnamed: CR1.3, F11.134
unnamed: CR1.5, F11.135
unnamed: CR1.7, F11.136
unnamed: CR1.9, F11.137
unnamed: CR2.3, F11.138
unnamed: CR2.5, F11.139
unnamed: CR2.7, F11.140
unnamed: CR2.9, F11.141
unnamed: CR3.3, F11.143
unnamed: CR3.5, F11.144
unnamed: CR3.7, F11.145
unnamed: CR3.9, F11.146
unnamed: CR4.3, F11.148
unnamed: CR4.5, F11.149
unnamed: CR4.7, F11.150
unnamed: CR4.9, F11.151
unnamed: CR5.3, F11.152
unnamed: CR5.5, F11.153
unnamed: CR5.7, F11.154
unnamed: CR5.9, F11.155
unnamed: CR6.3, F11.156
unnamed: CR6.5, F11.157
unnamed: CR6.7, F11.158
unnamed: CR6.9, F11.159
unnamed: CR7.3, F11.167
unnamed: CR7.5, F11.168
unnamed: CR7.7, F11.169
unnamed: CR8.3, F11.123
unnamed: CR8.5, F11.124
unnamed: CR8.7, F11.127
unnamed: CR8.9, F11.128
unnamed: CR9.3, F11.118
unnamed: CR9.5, F11.120
unnamed: CR9.7, F11.121
unnamed: CR9.9, F11.122
unnamed: CR10.3, F11.129
unnamed: CR10.5, F11.131
unnamed: CR10.7, F11.132
unnamed: CR10.9, F11.133
unnamed: CR11.3, F11.162
unnamed: CR11.5, F11.163
unnamed: D7.4, G2.15
unnamed: E13.1, F11.74
unnamed: E13.3, F11.72
unnamed: E13.4, F11.71
unnamed: E13.2, F11.73
unnamed: J11.135, J11.140
unnamed: J13.36, J13.45, J13.47
unnamed: J13.198, J13.203, J13.206, J13.207, J13.208
unnamed: K14.9, K14.10
unnamed: SCU3.122, T4.8
unnamed: T1.10, T1.11
unnamed: T4.10, T4.11
VCC: A4.8, A5.8, B3.6, C5.13, CR1.1, CR2.1, CR3.1, CR4.1, CR5.1, CR6.1, CR7.1, CR8.1, CR9.1, CR10.1, CR11.1, D1.1, D1.6, D1.20, D2.1, D2.6, D2.21, D3.1, D3.6, D3.21, D4.1, D4.6, D4.21, D5.1, D5.6, D5.21, D6.24, D7.24, D8.24, D9.24, D10.24, E8.8, E8.24, E9.8, E9.24, E13.6, E13.8, F9.28, F11.2, F11.6, F11.10, F11.15, F11.28, F11.38, F11.43, F11.47, F11.53, F11.56, F11.60, F11.61, F11.62, F11.75, F11.81, F11.96, F11.97, F11.104, F11.106, F11.108, F12.9, F12.12, F12.13, G2.9, G2.12, G2.16, G2.17, G2.20, G2.24, G2.26, G2.39, G2.57, G2.96, G2.123, G2.144, G2.147, G2.150, G2.152, G2.153, G2.155, G2.158, G2.161, G2.181, G2.201, G2.220, G2.221, G2.226, G2.228, G2.229, G2.248, G6.4, G6.18, G6.54, G6.55, G6.60, G6.70, G6.75, G6.83, G6.90, G6.91, G6.95, G6.100, G6.113, G6.127, G6.129, G6.130, G8.13, G8.33, G8.51, G8.73, H1.24, H2.24, H3.24, H4.24, H5.7, H5.18, H5.31, H5.42, H6.7, H6.18, H6.31, H6.42, H9.7, H9.18, H9.31, H9.42, J11.9, J11.18, J11.19, J11.25, J11.34, J11.40, J11.44, J11.47, J11.54, J11.55, J11.58, J11.76, J11.77, J13.10, J13.43, J13.44, J13.60, J13.61, J13.114, J13.147, J13.164, J13.165, J13.201, J13.204, J13.205, J15.1, J15.6, J15.20, JE01.12, JE01.37, JE02.12, JE02.37, JE03.12, JE03.37, JE04.12, JE04.37, JE05.12, JE05.37, JE06.12, JE06.37, JE07.12, JE07.37, JE08.12, JE08.37, JE11.12, JE11.37, JE12.12, JE12.37, JE13.12, JE13.37, JE14.12, JE14.37, JE15.12, JE15.37, JE16.12, JE16.37, JE17.12, JE17.37, JE18.12, JE18.37, JE21.12, JE21.37, JE22.12, JE22.37, JE23.12, JE23.37, JE24.12, JE24.37, JE25.12, JE25.37, JE26.12, JE26.37, JE27.12, JE27.37, JE28.12, JE28.37, JE31.12, JE31.37, JE32.12, JE32.37, JE33.12, JE33.37, JE34.12, JE34.37, JE35.12, JE35.37, JE36.12, JE36.37, JE37.12, JE37.37, JE38.12, JE38.37, K14.27, K14.44, KA10.12, KA10.37, KA12.12, KA12.37, KA13.12, KA13.37, KA14.12, KA14.37, KB10.12, KB10.37, KB12.12, KB12.37, KB13.12, KB13.37, KB14.12, KB14.37, SCU3.67, SCU3.84, SCU3.96, SCU3.123, SCU3.132, SCU3.139, T1.1, T1.14, T4.9, T4.14, U1.14, U2.14, Z2.37, Z5.23, Z6.24
VSS: A4.4, A5.4, A13.9, A13.11, A13.13, A13.15, A14.2, A14.4, A14.6, A14.8, A14.9, A14.11, A14.13, A14.15, B3.4, C5.2, C5.3, C5.7, C5.9, C5.11, C5.23, C9.2, C9.6, C9.10, C9.11, C9.12, C9.18, C9.19, C9.20, C9.26, C9.34, C9.38, C9.42, C11.3, C11.4, C11.5, C11.6, C11.12, C11.13, C12.4, C12.5, C12.12, C12.13, CR1.10, CR2.10, CR3.10, CR4.10, CR5.10, CR6.10, CR7.10, CR8.10, CR9.10, CR10.10, CR11.10, D1.21, D1.27, D1.35, D1.40, D2.22, D2.37, D2.42, D3.22, D3.37, D3.42, D4.22, D4.37, D4.42, D5.22, D5.37, D5.42, D6.12, D6.13, D7.12, D7.13, D8.4, D8.8, D8.12, D8.14, D8.18, D8.22, D9.4, D9.8, D9.12, D9.14, D9.18, D9.22, D10.4, D10.8, D10.12, D10.14, D10.18, D10.22, E8.9, E8.25, E8.28, E9.9, E9.25, E9.28, E13.5, F9.14, F9.20, F9.22, F11.70, F11.82, F11.83, F11.85, F11.86, F11.103, F11.109, F11.112, F11.114, F11.119, F11.130, F11.142, F11.147, F11.160, F11.161, F11.164, F11.165, F11.166, F11.170, F11.179, F11.188, F11.200, F11.201, F11.207, F12.2, F12.7, G2.1, G2.3, G2.6, G2.38, G2.68, G2.71, G2.74, G2.76, G2.77, G2.79, G2.82, G2.85, G2.114, G2.115, G2.133, G2.172, G2.190, G2.191, G2.209, G2.210, G2.231, G2.234, G2.237, G6.11, G6.19, G6.38, G6.43, G6.44, G6.49, G6.69, G6.101, G6.106, G6.112, G6.126, G8.1, G8.6, G8.12, G8.18, G8.23, G8.27, G8.36, G8.41, G8.46, G8.52, G8.58, G8.60, G8.62, G8.65, G8.71, G8.76, H1.1, H1.12, H2.1, H2.12, H3.1, H3.12, H4.1, H4.12, H5.1, H5.4, H5.10, H5.15, H5.21, H5.24, H5.25, H5.26, H5.27, H5.28, H5.29, H5.30, H5.32, H5.33, H5.34, H5.39, H5.45, H5.48, H6.1, H6.4, H6.10, H6.15, H6.21, H6.24, H6.25, H6.28, H6.34, H6.39, H6.45, H6.48, H9.1, H9.4, H9.10, H9.15, H9.21, H9.24, H9.25, H9.28, H9.34, H9.39, H9.45, H9.48, J11.1, J11.33, J11.67, J11.90, J11.91, J11.99, J11.107, J11.110, J11.115, J11.120, J11.126, J11.127, J11.130, J11.136, J11.141, J11.144, J13.15, J13.26, J13.38, J13.76, J13.96, J13.97, J13.119, J13.129, J13.142, J13.174, J13.181, J13.200, J15.21, J15.27, J15.35, J15.40, JE01.35, JE01.36, JE02.35, JE02.36, JE03.35, JE03.36, JE04.35, JE04.36, JE05.35, JE05.36, JE06.35, JE06.36, JE07.35, JE07.36, JE08.35, JE08.36, JE11.35, JE11.36, JE12.35, JE12.36, JE13.35, JE13.36, JE14.35, JE14.36, JE15.35, JE15.36, JE16.35, JE16.36, JE17.35, JE17.36, JE18.35, JE18.36, JE21.35, JE21.36, JE22.35, JE22.36, JE23.35, JE23.36, JE24.35, JE24.36, JE25.35, JE25.36, JE26.35, JE26.36, JE27.35, JE27.36, JE28.35, JE28.36, JE31.35, JE31.36, JE32.35, JE32.36, JE33.35, JE33.36, JE34.35, JE34.36, JE35.35, JE35.36, JE36.35, JE36.36, JE37.35, JE37.36, JE38.35, JE38.36, K14.4, K14.23, K14.31, K14.39, KA10.35, KA10.36, KA12.35, KA12.36, KA13.35, KA13.36, KA14.35, KA14.36, KB10.35, KB10.36, KB12.35, KB12.36, KB13.35, KB13.36, KB14.35, KB14.36, SCU3.6, SCU3.14, SCU3.20, SCU3.26, SCU3.33, SCU3.42, SCU3.50, SCU3.56, SCU3.62, SCU3.69, SCU3.78, SCU3.86, SCU3.91, SCU3.98, SCU3.105, SCU3.106, SCU3.107, SCU3.110, SCU3.115, SCU3.120, SCU3.121, SCU3.134, SCU3.141, T1.7, T4.7, U1.7, U2.7, Z2.27, Z2.46, Z5.13, Z5.32, Z6.12, Z6.20
